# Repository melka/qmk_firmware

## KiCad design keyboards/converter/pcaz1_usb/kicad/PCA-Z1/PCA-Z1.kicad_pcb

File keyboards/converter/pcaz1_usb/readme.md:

# pcaz1_usb

*A short description of the keyboard/project*

* Keyboard Maintainer: [Kamel Makhloufi](https://github.com/yourusername)
* Hardware Supported: *The PCBs, controllers supported*
* Hardware Availability: *Links to where you can find this hardware*

Make example for this keyboard (after setting up your build environment):

    make pcaz1_usb:default

Flashing example for this keyboard:

    make pcaz1_usb:default:flash

See the [build environment setup](https://docs.qmk.fm/#/getting_started_build_tools) and the [make instructions](https://docs.qmk.fm/#/getting_started_make_guide) for more information. Brand new to QMK? Start with our [Complete Newbs Guide](https://docs.qmk.fm/#/newbs).

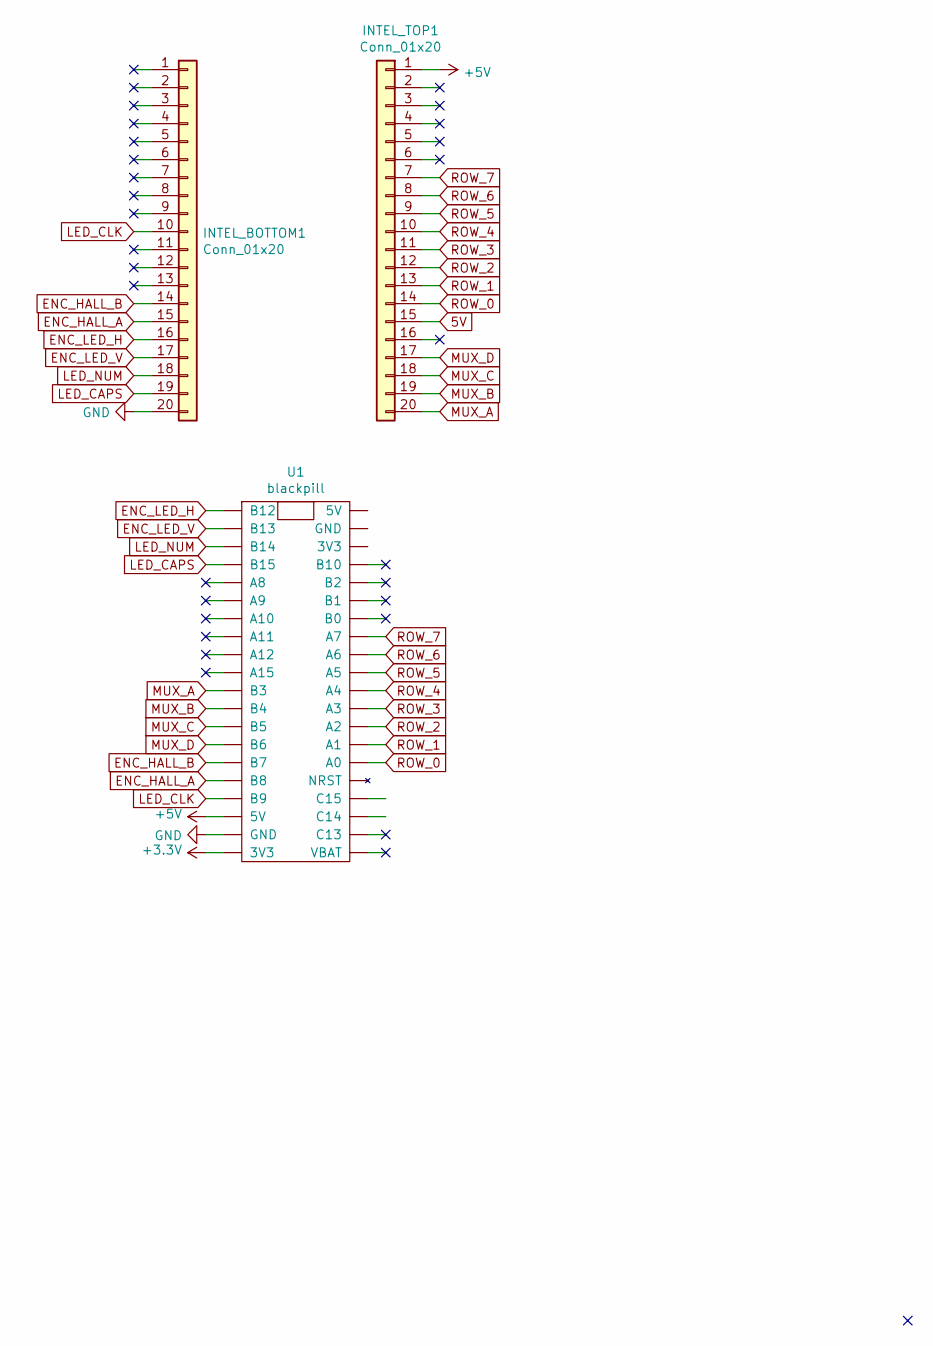
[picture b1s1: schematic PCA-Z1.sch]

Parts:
INTEL_BOTTOM1: Conn_01x20; PinHeader_1x20_P2.54mm_Vertical
INTEL_TOP1: Conn_01x20; PinHeader_1x20_P2.54mm_Vertical
U1: blackpill

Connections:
5V: INTEL_TOP1.15
+3V3: U1.20 (3V3)
+5V: INTEL_TOP1.1, U1.18 (5V)
ENC_HALL_A: INTEL_BOTTOM1.15, U1.16 (B8)
ENC_HALL_B: INTEL_BOTTOM1.14, U1.15 (B7)
ENC_LED_H: INTEL_BOTTOM1.16, U1.1 (B12)
ENC_LED_V: INTEL_BOTTOM1.17, U1.2 (B13)
GND: INTEL_BOTTOM1.20, U1.19 (GND)
LED_CAPS: INTEL_BOTTOM1.19, U1.4 (B15)
LED_CLK: INTEL_BOTTOM1.10, U1.17 (B9)
LED_NUM: INTEL_BOTTOM1.18, U1.3 (B14)
MUX_A: INTEL_TOP1.20, U1.11 (B3)
MUX_B: INTEL_TOP1.19, U1.12 (B4)
MUX_C: INTEL_TOP1.18, U1.13 (B5)
MUX_D: INTEL_TOP1.17, U1.14 (B6)
ROW_0: INTEL_TOP1.14, U1.26 (A0)
ROW_1: INTEL_TOP1.13, U1.27 (A1)
ROW_2: INTEL_TOP1.12, U1.28 (A2)
ROW_3: INTEL_TOP1.11, U1.29 (A3)
ROW_4: INTEL_TOP1.10, U1.30 (A4)
ROW_5: INTEL_TOP1.9, U1.31 (A5)
ROW_6: INTEL_TOP1.8, U1.32 (A6)
ROW_7: INTEL_TOP1.7, U1.33 (A7)

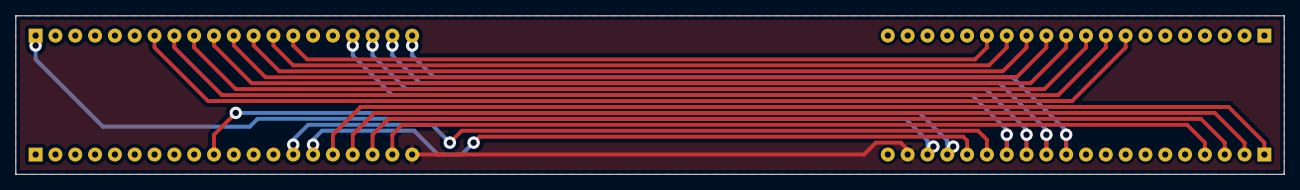
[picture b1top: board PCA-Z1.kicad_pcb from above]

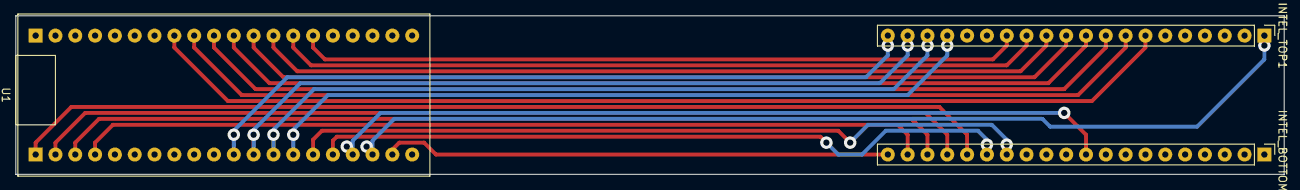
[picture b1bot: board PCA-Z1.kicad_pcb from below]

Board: 2 copper layers, 162.6 x 20.3 mm, 3 parts (3 on the bottom side), 21 nets.

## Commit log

2020-05-19 Preliminary work on adding NRF24 support
2020-05-19 Added fork of RF24 to simplify
2020-05-19 Commiting before branching to dev in userspace
2020-05-20 Started working on nrf24
    nrf24 connection needs to be implemented in the lufa folder because I can’t find a way to override the send_keyboard method…
2020-05-29 Init, config and pair works, huge lag on keypresses
2020-06-20 Save before switching branch
2020-12-26 - Switched the default USB_HID_ENABLE flag from yes to no since it doesn’t seem to be of use - Moved the definition of iso layout from a static in matric.c to a define in keymap config.h - Added my l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
2021-01-13 Fix functions when NO_ACTION_TAPPING is defined
2021-01-23 Added new keymap for AEK
2021-02-10 Added emoji keys
2021-02-21 removed debug mode
2021-02-21 Basic matrix reading
2021-02-22 basic matrix logic working, added PCB
2021-02-22 Routed PCB for home etching
2021-03-14 Added kicad PCB, matrix mapped
2021-03-14 adbtiny working, NO_ACTION_TAPPING removes layers
2021-03-14 Layers working
2021-03-14 Reenabled extrakey
